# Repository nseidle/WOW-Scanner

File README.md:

Grocery Scanner
=======

Grocery scanner is an interactive exhibit at the [WOW kid's museum](http://www.wowchildrensmuseum.org/) in Lafayette, CO. Sliding a plastic fruit, empty box, or even your hand causes the scanner to turn on a bright red LED and beep with that satisfying grocery store checkout beep.

This exhibit was created by Chris Francis and has been maintained by Nathan Seidle. It is a tremendously popular exhibit. Kids really enjoy being able to do what their parents do at the store.

The scanner is flush mounted to a low height checkout counter for small kids. The electronics are placed in a metal box with a clear acrylic cover. The cover in this picture has had 4 years of significant wear and tear but the IR distance sensor continues to function without problems.

This exhibit is rock solid and had been running for multiple years without maintenance.

License Information
-------------------

The hardware design and firmware are released under [Creative Commons Share-alike 3.0](http://creativecommons.org/licenses/by-sa/3.0/).  

Feel free to create your own copy of the Grocery Scanner. All I ask is that you include attribution of 'Based on the Grocery Scanner by Chris Francis'.

Repository Contents
-------------------
* **/hardware** - Unproven Eagle PCB layouts for an Arduino shield 
* **/firmware** - The sketch that runs on the Arduino Pro 
* **/images** - Images and a video of the scanner in use

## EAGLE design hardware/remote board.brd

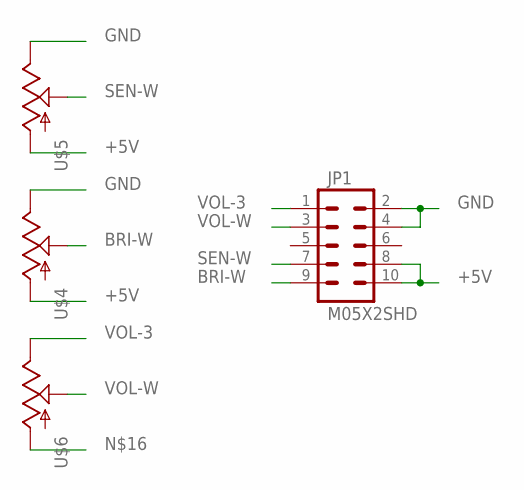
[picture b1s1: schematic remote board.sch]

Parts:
JP1: M05X2SHD; 2X5-SHROUDED
U$4, U$5, U$6: POT100K_3362U; 3362U

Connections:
+5V: JP1.8, JP1.10, U$4.P$3 (A), U$5.P$3 (A)
BRI-W: JP1.9, U$4.P$2 (S)
GND: JP1.2, JP1.4, U$4.P$1 (E), U$5.P$1 (E)
SEN-W: JP1.7, U$5.P$2 (S)
VOL-3: JP1.1, U$6.P$1 (E)
VOL-W: JP1.3, U$6.P$2 (S)

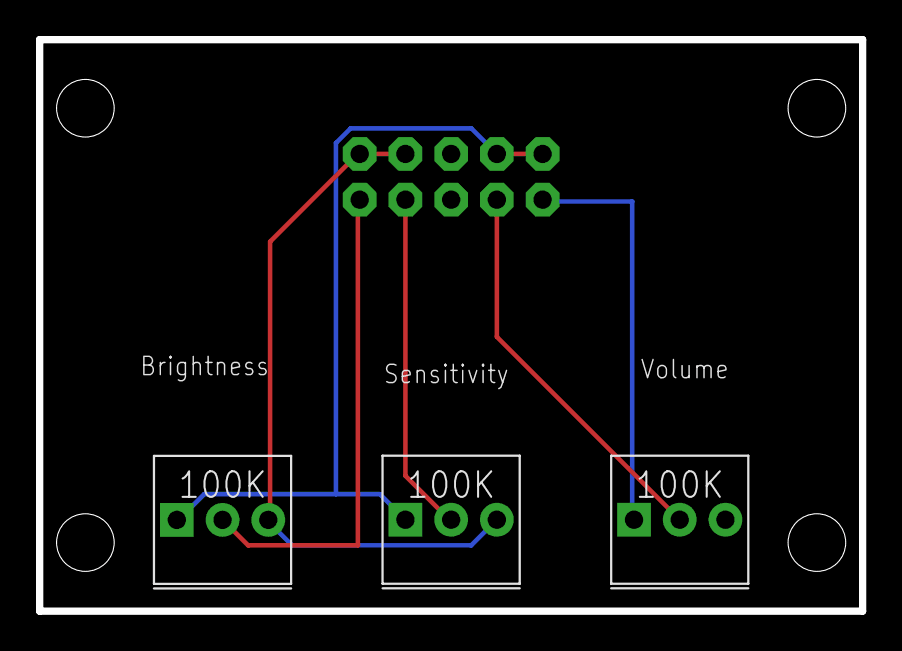
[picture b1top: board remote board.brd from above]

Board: 2 copper layers, 45.7 x 31.8 mm, 4 parts (1 on the bottom side), 6 nets.

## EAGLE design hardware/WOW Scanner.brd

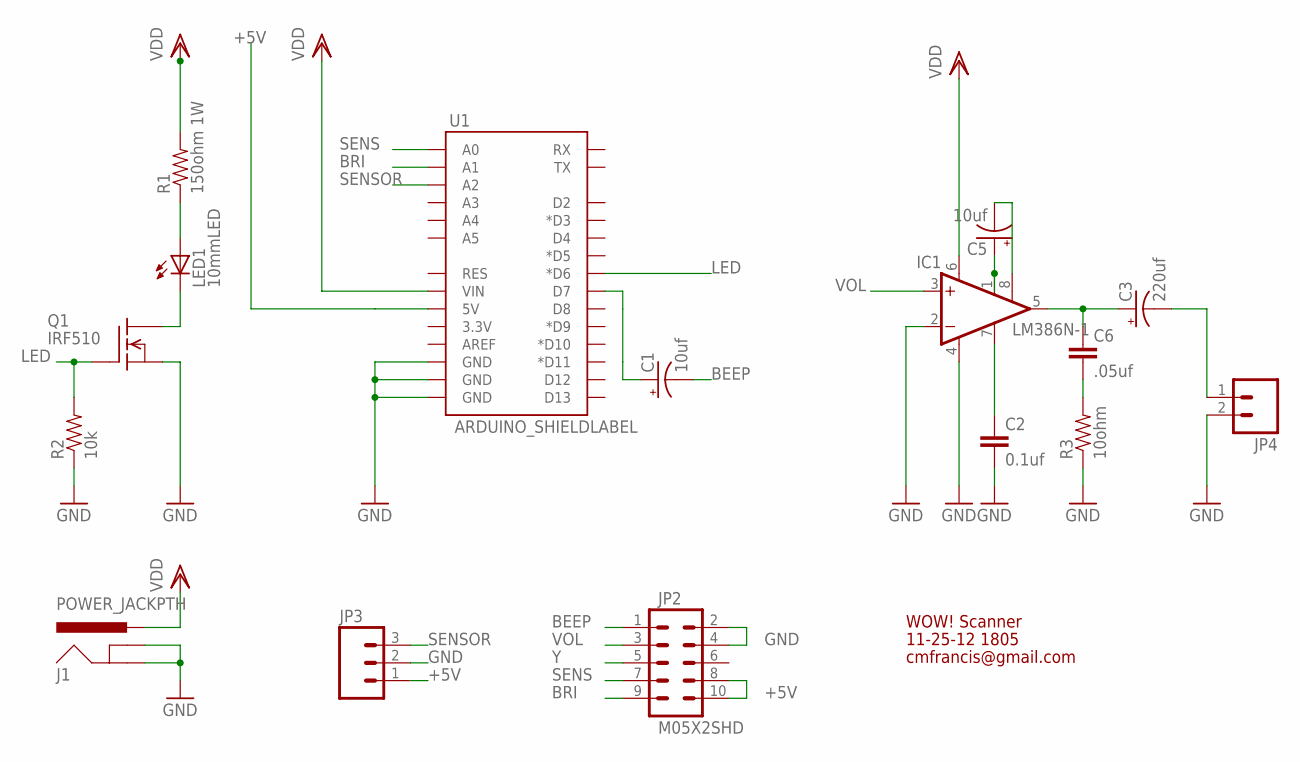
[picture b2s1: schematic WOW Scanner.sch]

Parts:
C1, C5: 10uf; CPOL-RADIAL-10UF-25V
C2: 0.1uf; CAP-PTH-SMALL
C3: 220uf; CPOL-RADIAL-100UF-25V
C6: .05uf; CAP-PTH-SMALL
IC1: LM386N-1; DIL08
J1: POWER_JACKPTH; POWER_JACK_PTH
JP2: M05X2SHD; 2X5-SHROUDED
JP3: M03JST-PTH; JST-3-PTH
JP4: M02PTH; 1X02
LED1: 10mmLED; LED10MM
Q1: IRF510; TO220
R1: 150ohm 1W; AXIAL-0.6
R2: 10k; AXIAL-0.4
R3: 10ohm; AXIAL-0.4
U1: ARDUINO_SHIELDLABEL; DUEMILANOVE_SHIELD

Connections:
+5V: JP2.8, JP2.10, JP3.1, U1.5V
BEEP: C1.2 (-), JP2.1
BRI: JP2.9, U1.A1
GND: C2.2, IC1.2 (-IN), IC1.4 (GND), J1.GND, J1.GNDBREAK, JP2.2, JP2.4, JP3.2, JP4.2, Q1.3 (S), R2.P$1 (1), R3.P$1 (1), U1.GND@0 (GND), U1.GND@1 (GND), U1.GND@2 (GND)
LED: Q1.1 (G), R2.P$2 (2), U1.D6 (*D6)
unnamed: LED1.A, R1.P$1 (1)
unnamed: LED1.C, Q1.2 (D)
unnamed: C2.1, IC1.7 (BYPASS)
unnamed: C6.2, R3.P$2 (2)
unnamed: C3.1 (+), C6.1, IC1.5 (OUT)
unnamed: C5.1 (+), IC1.1 (GAIN)
unnamed: C5.2 (-), IC1.8 (GAIN)
unnamed: C3.2 (-), JP4.1
unnamed: C1.1 (+), U1.D7
SENS: JP2.7, U1.A0
SENSOR: JP3.3, U1.A2
VDD: IC1.6 (VS), J1.PWR, R1.P$2 (2), U1.VIN
VOL: IC1.3 (+IN), JP2.3
Y: JP2.5

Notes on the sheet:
WOW! Scanner
11-25-12 1805
cmfrancis@gmail.com

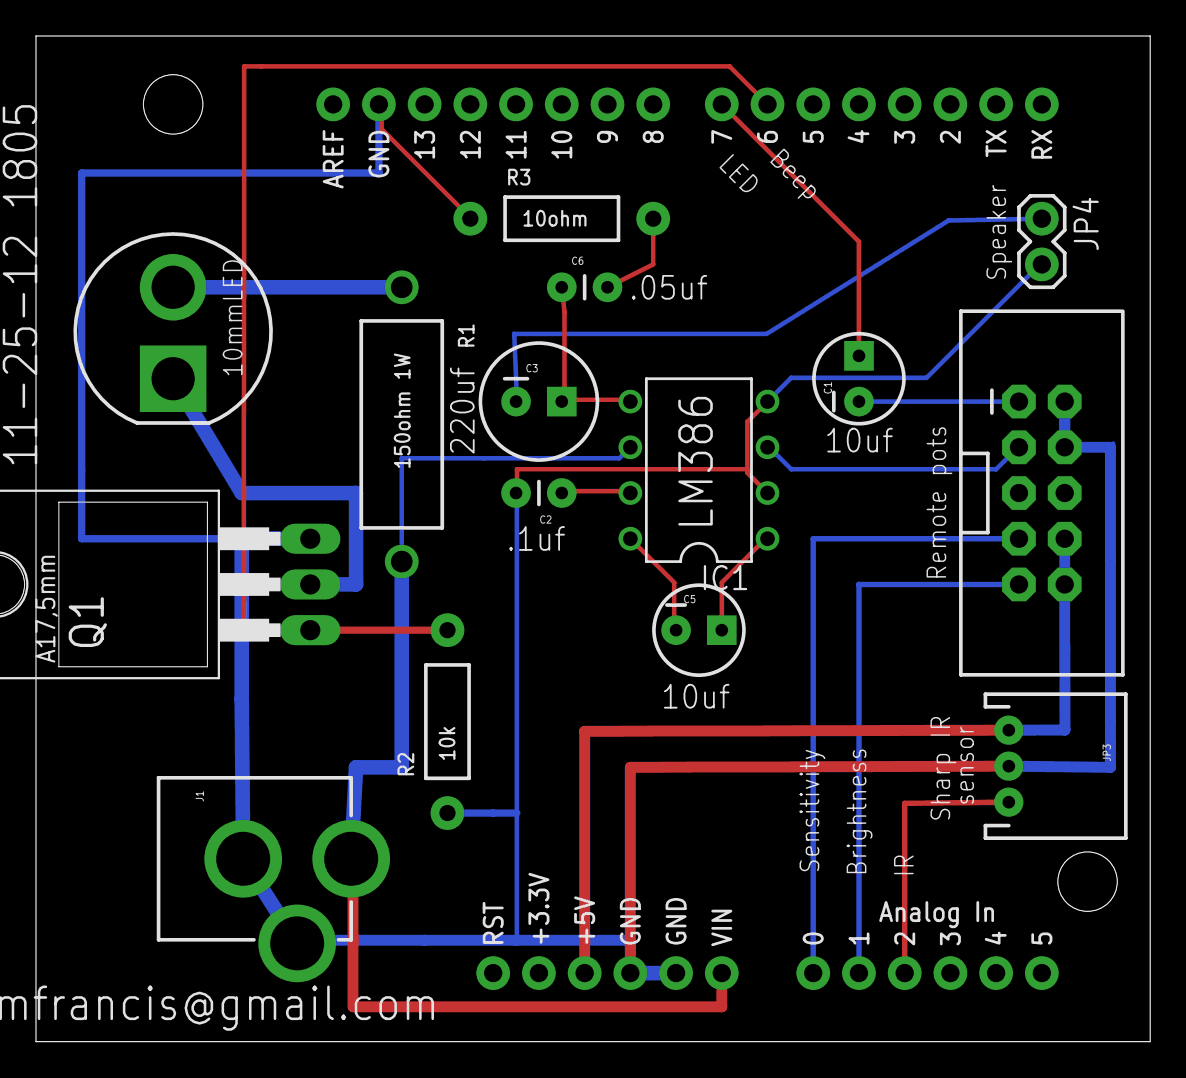
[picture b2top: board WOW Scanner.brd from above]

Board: 2 copper layers, 61.9 x 55.9 mm, 16 parts (0 on the bottom side), 18 nets.

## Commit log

2013-04-22 Upgraded sketch to INO file. Updated directory structure.
    No code changes. Added a small todo (add a watch dog and reset someday).
2013-04-22 Added a function to average sensor readings.
2013-04-29 Removed trimpot checking.
    The hardware trimpots where not working (defective cable) so they were
    removed and replaced with a volume knob directly on the amp and a hard
    coded threshold value.
2016-03-09 Adding more documentation and photos

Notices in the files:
parts and their libraries:
SparkFun: Licensing: CC v3.0 Share-Alike You are welcome to use this library for commercial purposes.
